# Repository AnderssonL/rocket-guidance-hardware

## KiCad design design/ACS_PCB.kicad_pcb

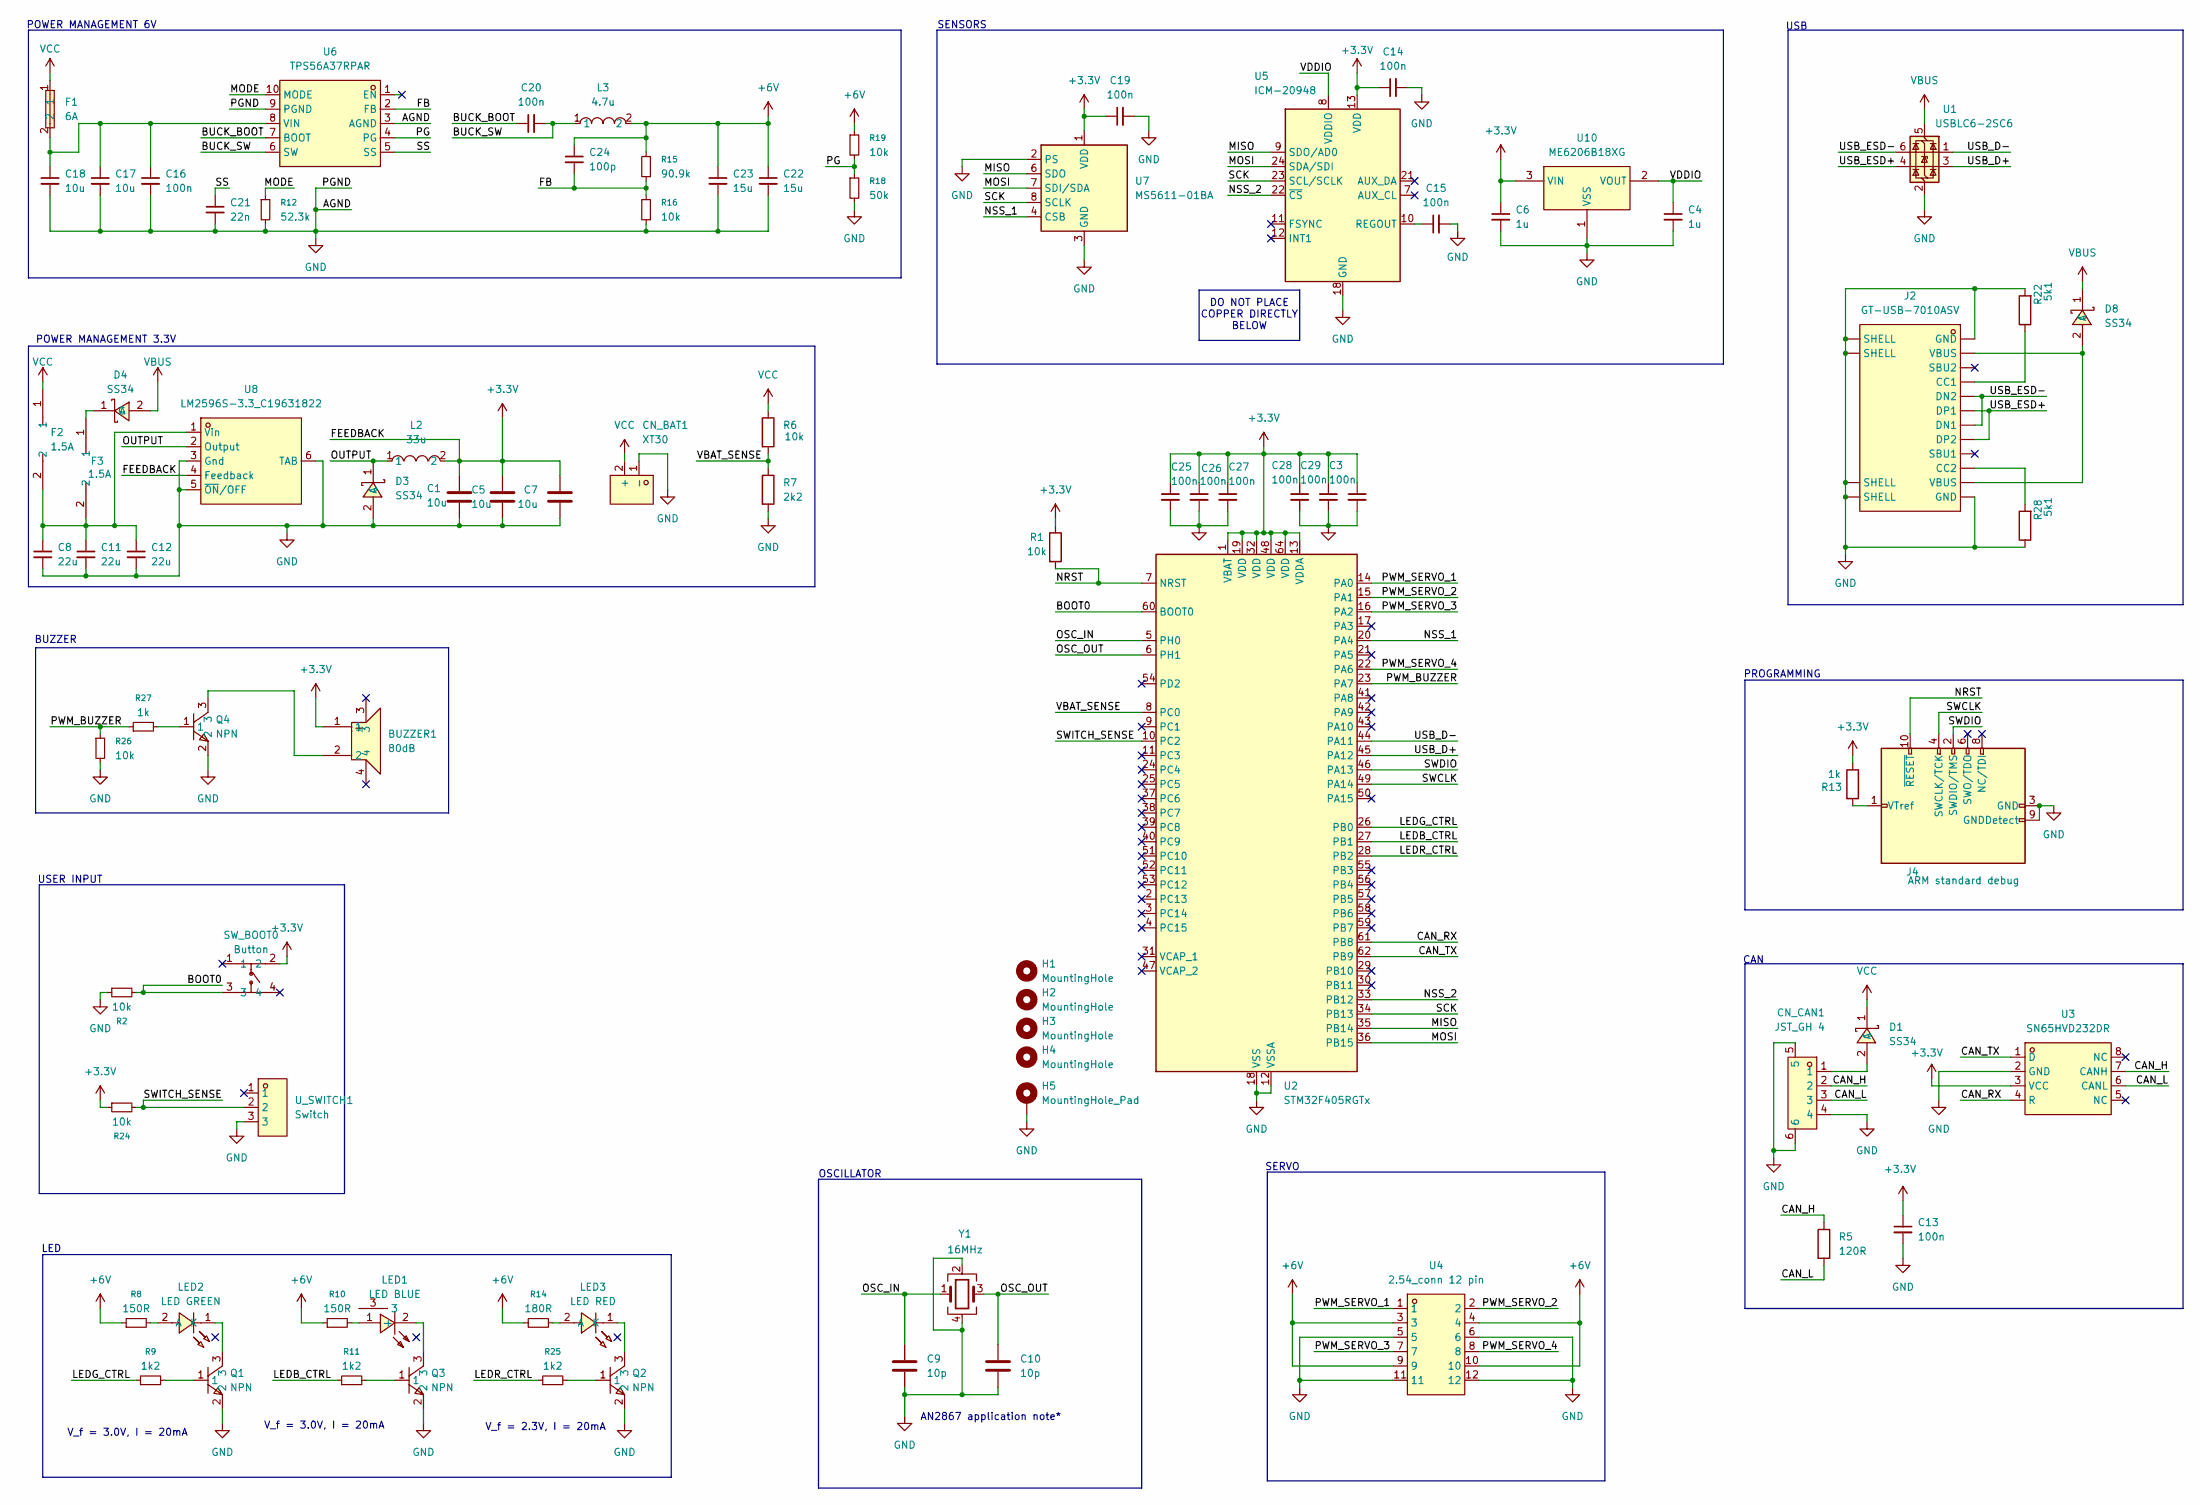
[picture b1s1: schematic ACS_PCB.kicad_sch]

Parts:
BUZZER1: 80dB; BUZ-SMD_4P-L7.5-W7.5-BR; LCSC Part C49246950
C1, C5, C7: 10u; C_0201_0603Metric; LCSC Part C19702
C3, C13, C14, C15, C16, C19, C20, C25, C26, C27, C28, C29: 100n; C_0603_1608Metric; LCSC Part C14663
C4, C6: 1u; C_0603_1608Metric; LCSC Part C15849
C8, C11, C12: 22u; C_0603_1608Metric; LCSC Part C2762594
C9, C10: 10p; C_0603_1608Metric; LCSC Part C1634
C17, C18: 10u; C_0603_1608Metric; LCSC Part C19702
C21: 22n; C_0603_1608Metric; LCSC Part C21122
C22, C23: 15u; C_0603_1608Metric; LCSC Part C445715
C24: 100p; C_0603_1608Metric; LCSC Part C14858
CN_BAT1: XT30; CONN-TH_XT30UPB-M; LCSC Part C428721
CN_CAN1: JST_GH 4; CONN-SMD_4P-P1.25_JXTCONN_DMX-4PWB-43; LCSC Part C42422450
D1, D3, D4, D8: SS34; SMC_L6.9-W5.9-LS7.9-RD; LCSC Part C154551
F1: 6A; F1812; LCSC Part C7542974
F2, F3: 1.5A; F1812; LCSC Part C70117
H1, H2, H3, H4: MountingHole; SMD_BD4.0-D2.5_TH162030CTJ; LCSC Part C3020127
H5: MountingHole_Pad; MountingHole_2.2mm_M2_DIN965_Pad
J2: GT-USB-7010ASV; USB-C-SMD_G-SWITCH_GT-USB-7010ASV; LCSC Part C2988369
J4: ARM standard debug; HDR-SMD_10P-P1.27-V-R2-C5-S5.8; LCSC Part C5155080
L2: 33u; IND-SMD_L6.8-W6.8_SMMS0630; LCSC Part C149577
L3: 4.7u; L0603; LCSC Part C114862
LED1: LED BLUE; LED-SMD_L3.2-W1.0-R-RD; LCSC Part C375481
LED2: LED GREEN; LED1206-RD_GREEN-SIDE; LCSC Part C375564
LED3: LED RED; LED1206-RD_RED_XL-3216SURC-FB; LCSC Part C3646938
Q1, Q2, Q3, Q4: NPN; SOT-23-3_L2.9-W1.3-P1.90-LS2.4-BR; LCSC Part C57668
R1, R2, R6, R16, R19, R24, R26: 10k; R_0603_1608Metric; LCSC Part C98220
R5: 120R; R_0603_1608Metric; LCSC Part C22787
R7: 2k2; R_0603_1608Metric; LCSC Part C114662
R8, R10: 150R; R_0603_1608Metric; LCSC Part C2907103
R9, R11, R25: 1k2; R_0603_1608Metric; LCSC Part C2906976
R12: 52.3k; R_0603_1608Metric; LCSC Part C2998074
R13, R27: 1k; R_0603_1608Metric; LCSC Part C22548
R14: 180R; R_0603_1608Metric; LCSC Part C2907000
R15: 90.9k; R_0603_1608Metric; LCSC Part C2930136
R18: 50k; R_0603_1608Metric; LCSC Part C861451
R22, R28: 5k1; R_0603_1608Metric; LCSC Part C2907044
SW_BOOT0: Button; SW-SMD_4P-L5.2-W5.2-P3.70-LS6.4; LCSC Part C49234134
U1: USBLC6-2SC6; SOT-23-6_L2.9-W1.6-P0.95-LS2.8-BL; LCSC Part C7519
U2: STM32F405RGTx; LQFP-64_10x10mm_P0.5mm; LCSC Part C15742
U3: SN65HVD232DR; SOIC-8_L5.0-W4.0-P1.27-LS6.0-BL; LCSC Part C30530
U4: 2.54_conn 12 pin; HDR-TH_12P-P2.54-V-M-R2-C6-S2.54; LCSC Part C7501277
U5: ICM-20948; InvenSense_QFN-24_3x3mm_P0.4mm
U6: TPS56A37RPAR; VQFN-HR-10_L3.0-W3.0_TI_RPA; LCSC Part C22392669
U7: MS5611-01BA; SENSORS-SMD_MS5611-01BA03; LCSC Part C15639
U8: LM2596S-3.3_C19631822; TO-263-5_L10.2-W9.0-P1.70-TL-LS15.2; LCSC Part C19631822
U10: ME6206B18XG; SOT-23-3_L2.9-W1.3-P1.90-LS2.4-BR; LCSC Part C2683407
U_SWITCH1: Switch; SW-TH_MT-0-102-E001-T000-RS-PJ; LCSC Part C1788499
Y1: 16MHz; CRYSTAL-SMD_4P-L3.2-W2.5-BL; LCSC Part C112972

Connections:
+3.3V: BUZZER1.1, C1.1, C3.1, C5.1, C6.1, C7.1, C13.1, C14.1, C19.1, C25.1, C26.1, C27.1, C28.1, C29.1, L2.2, R1.1, R13.1, R24.1, SW_BOOT0.2, U2.1 (VBAT), U2.13 (VDDA), U2.19 (VDD), U2.32 (VDD), U2.48 (VDD), U2.64 (VDD), U3.3 (VCC), U5.13 (VDD), U7.1 (VDD), U8.4 (Feedback), U10.3 (VIN)
+6V: C22.1, C23.1, C24.1, L3.2, R8.1, R10.1, R14.1, R15.2, R19.1, U4.3, U4.4, U4.9, U4.10
/BOOT0: R2.2, SW_BOOT0.3, U2.60 (BOOT0)
/BUCK_BOOT: C20.1, U6.7 (BOOT)
/BUCK_SW: C20.2, L3.1, U6.6 (SW)
/CAN_H: CN_CAN1.2, R5.1, U3.7 (CANH)
/CAN_L: CN_CAN1.3, R5.2, U3.6 (CANL)
/CAN_RX: U2.61 (PB8), U3.4 (R)
/CAN_TX: U2.62 (PB9), U3.1 (D)
/FB: C24.2, R15.1, R16.2, U6.2 (FB)
/LEDB_CTRL: R11.1, U2.27 (PB1)
/LEDG_CTRL: R9.1, U2.26 (PB0)
/LEDR_CTRL: R25.1, U2.28 (PB2)
/MISO: U2.35 (PB14), U5.9 (SDO/AD0), U7.6 (SDO)
/MODE: R12.1, U6.10 (MODE)
/MOSI: U2.36 (PB15), U5.24 (SDA/SDI), U7.7 (SDI/SDA)
/NRST: J4.10 (~RESET), R1.2, U2.7 (NRST)
/NSS_1: U2.20 (PA4), U7.4 (CSB), U7.5 (CSB)
/NSS_2: U2.33 (PB12), U5.22 (~CS)
/OSC_IN: C9.1, U2.5 (PH0), Y1.1
/OSC_OUT: C10.1, U2.6 (PH1), Y1.3
/OUTPUT: D3.1 (C), L2.1, U8.2 (Output)
/PG: R18.1, R19.2, U6.4 (PG)
/PWM_BUZZER: R26.1, R27.1, U2.23 (PA7)
/PWM_SERVO_1: U2.14 (PA0), U4.1
/PWM_SERVO_2: U2.15 (PA1), U4.2
/PWM_SERVO_3: U2.16 (PA2), U4.7
/PWM_SERVO_4: U2.22 (PA6), U4.8
/SCK: U2.34 (PB13), U5.23 (SCL/SCLK), U7.8 (SCLK)
/SS: C21.1, U6.5 (SS)
/SWCLK: J4.4 (SWCLK/TCK), U2.49 (PA14)
/SWDIO: J4.2 (SWDIO/TMS), U2.46 (PA13)
/SWITCH_SENSE: R24.2, U2.10 (PC2), U_SWITCH1.2
/USB_D+: U1.3 (I/O2), U2.45 (PA12)
/USB_D-: U1.1 (I/O1), U2.44 (PA11)
/USB_ESD+: J2.A6 (DP1), J2.B6 (DP2), U1.4 (I/O2)
/USB_ESD-: J2.A7 (DN1), J2.B7 (DN2), U1.6 (I/O1)
/VBAT_SENSE: R6.2, R7.1, U2.8 (PC0)
/VDDIO: C4.1, U5.8 (VDDIO), U10.2 (VOUT)
GND: C1.2, C3.2, C4.2, C5.2, C6.2, C7.2, C8.2, C9.2, C10.2, C11.2, C12.2, C13.2, C14.2, C15.2, C16.2, C17.2, C18.2, C19.2, C21.2, C22.2, C23.2, C25.2, C26.2, C27.2, C28.2, C29.2, CN_BAT1.1 (-), CN_CAN1.4, CN_CAN1.5, CN_CAN1.6, D3.2 (A), H5.1, J2.1 (SHELL), J2.2 (SHELL), J2.3 (SHELL), J2.4 (SHELL), J2.A1B12 (GND), J2.B1A12 (GND), J4.3 (GND), J4.5 (GND), J4.9 (GNDDetect), Q1.2, Q2.2, Q3.2, Q4.2, R2.1, R7.2, R12.2, R16.1, R18.2, R22.2, R26.2, R28.1, U1.2 (GND), U2.12 (VSSA), U2.18 (VSS), U2.63 (VSS), U3.2 (GND), U4.5, U4.6, U4.11, U4.12, U5.18 (GND), U5.20 (GND), U6.3 (AGND), U6.9 (PGND), U7.2 (PS), U7.3 (GND), U8.3 (Gnd), U8.5 (~ON/OFF), U8.6 (TAB), U10.1 (VSS), U_SWITCH1.3, Y1.2, Y1.4
unnamed: BUZZER1.2, Q4.3
unnamed: CN_CAN1.1, D1.2 (A)
unnamed: D4.1 (C), F3.1
unnamed: D8.2 (A), J2.A4B9 (VBUS), J2.B4A9 (VBUS)
unnamed: J2.A5 (CC1), R22.1
unnamed: J2.B5 (CC2), R28.2
unnamed: J4.1 (VTref), R13.2
unnamed: LED1.1 (+), R10.2
unnamed: LED1.2 (-), Q3.3
unnamed: LED2.2 (A), R8.2
unnamed: LED2.1 (K), Q1.3
unnamed: LED3.2 (A), R14.2
unnamed: LED3.1 (K), Q2.3
unnamed: Q1.1, R9.2
unnamed: Q2.1, R25.2
unnamed: Q3.1, R11.2
unnamed: Q4.1, R27.2
unnamed: C15.1, U5.10 (REGOUT)
unnamed: C16.1, C17.1, C18.1, F1.2, U6.8 (VIN)
unnamed: C8.1, C11.1, C12.1, F2.2, F3.2, U8.1 (Vin)
VBUS: D4.2 (A), D8.1 (C), U1.5 (VBUS)
VCC: CN_BAT1.2 (+), D1.1 (C), F1.1, F2.1, R6.1

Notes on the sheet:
V_f = 3.0V, I = 20mA
BUZZER
SENSORS
USER INPUT
V_f = 2.3V, I = 20mA
LED
POWER MANAGEMENT 6V
POWER MANAGEMENT 3.3V
DO NOT PLACE COPPER DIRECTLY BELOW
OSCILLATOR
SERVO
USB
AN2867 application note*
CAN
PROGRAMMING

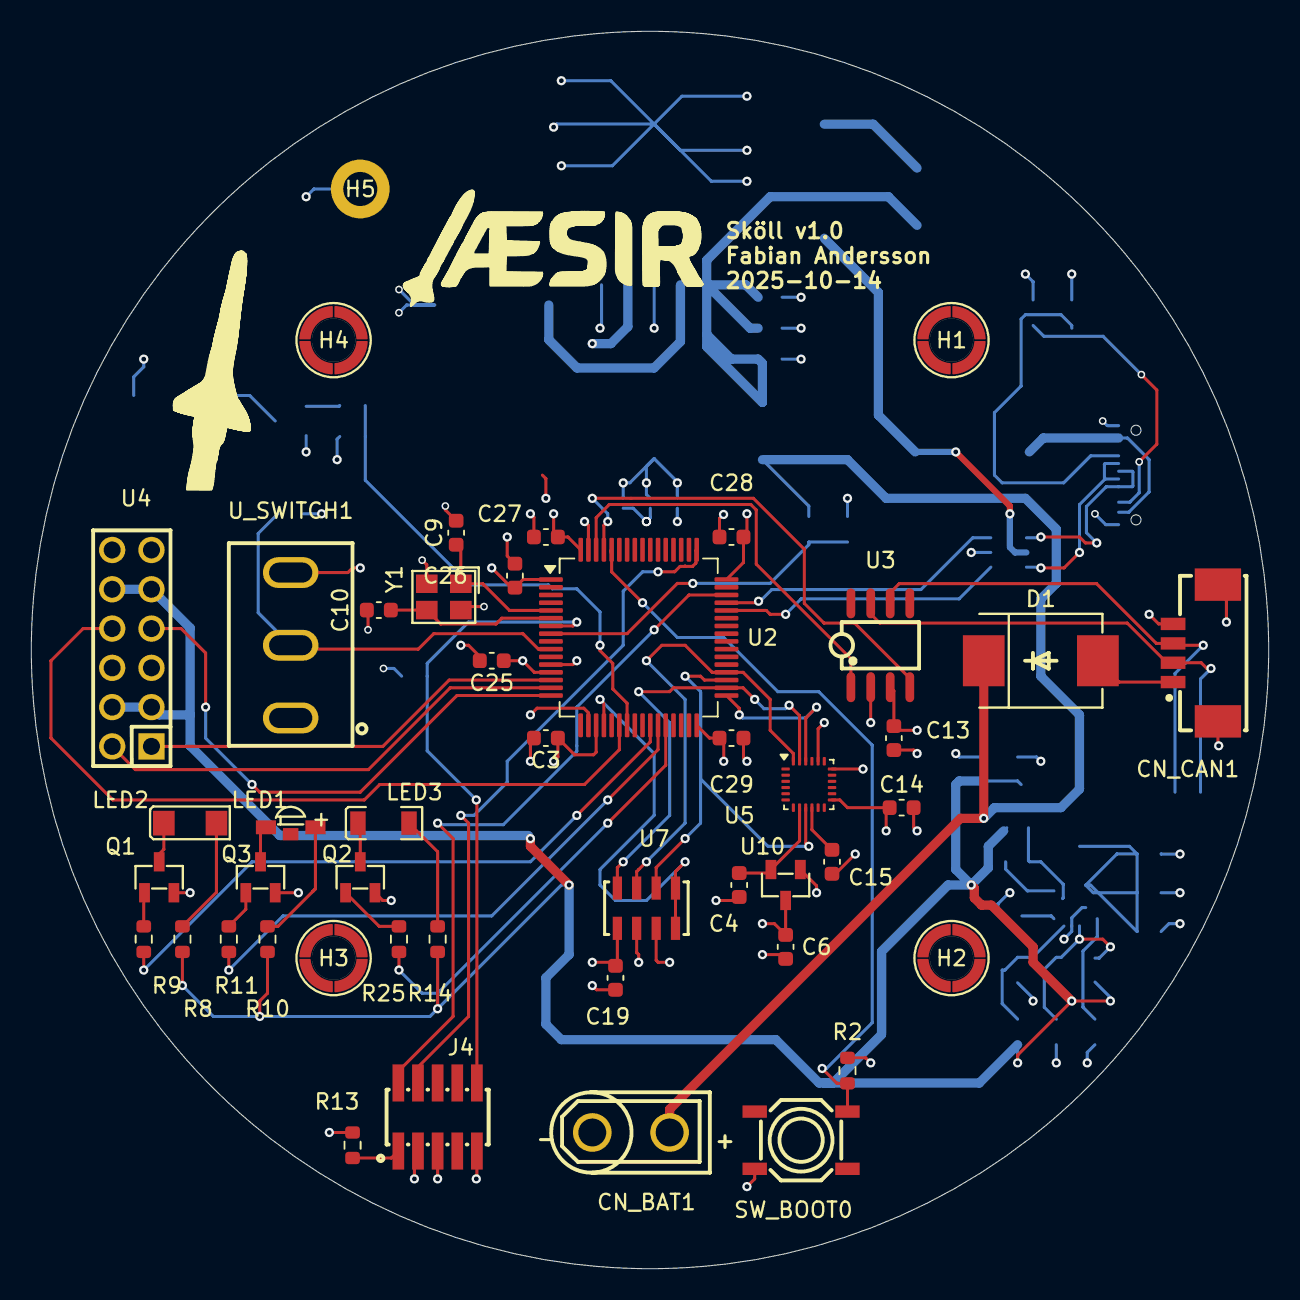
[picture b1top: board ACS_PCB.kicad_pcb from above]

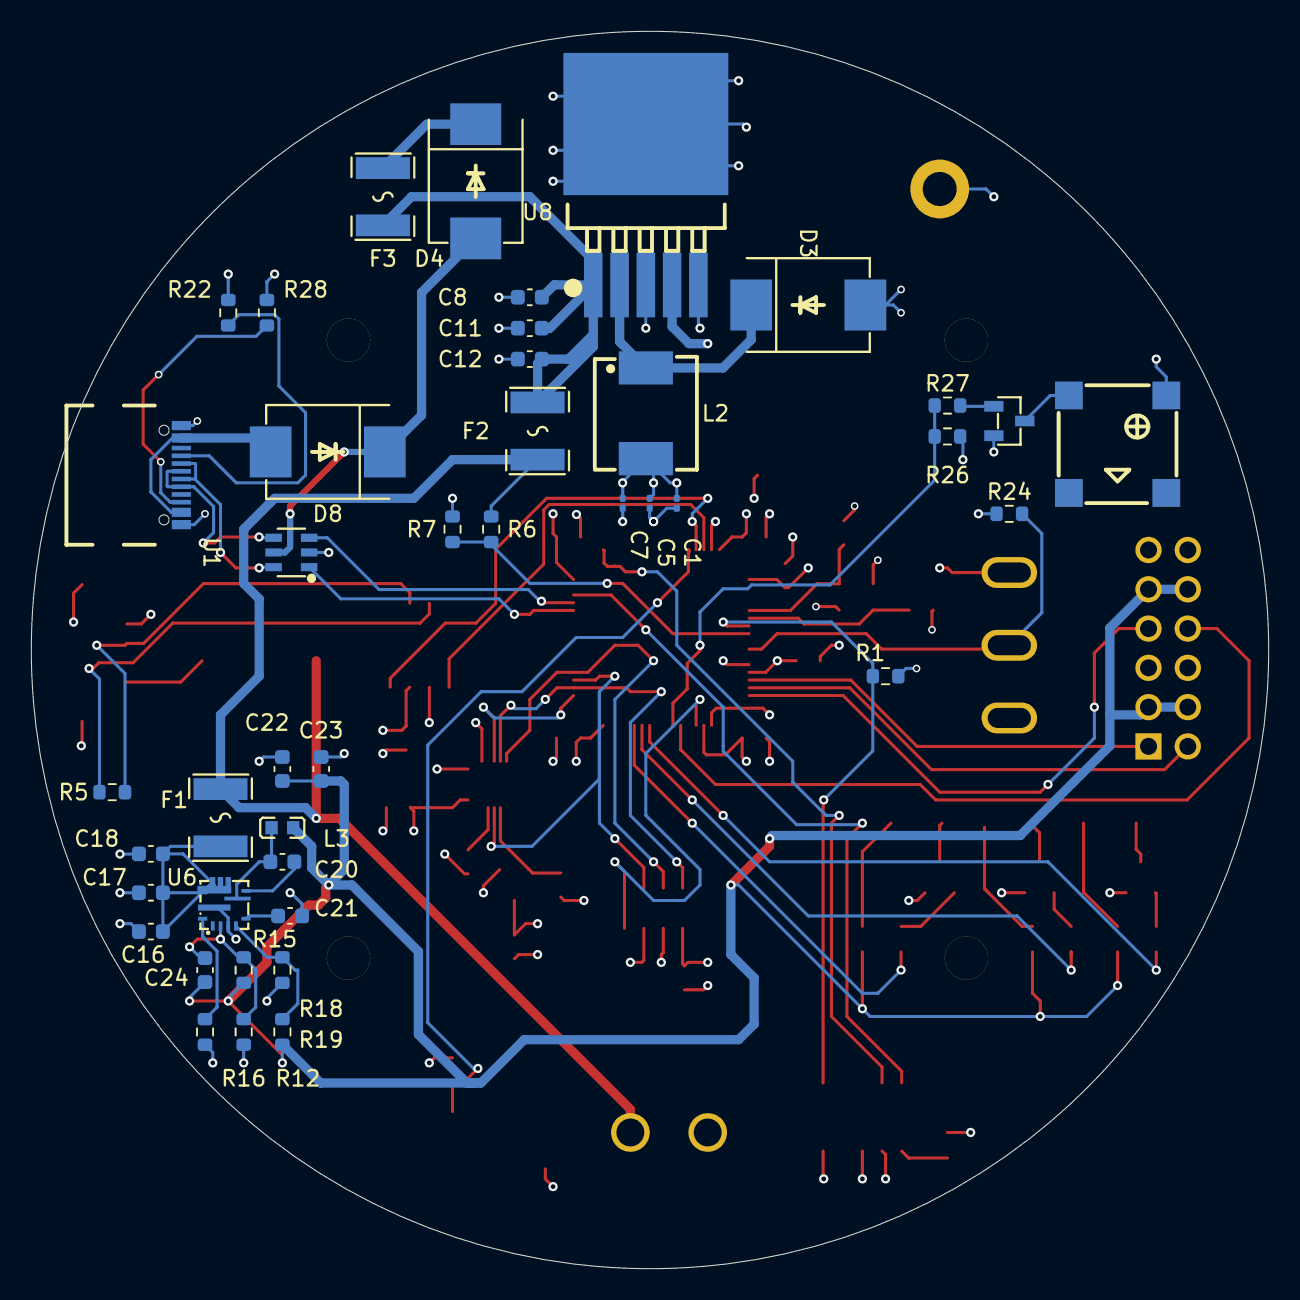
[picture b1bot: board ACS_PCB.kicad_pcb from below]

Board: 4 copper layers, 80.0 x 80.0 mm, 88 parts (42 on the bottom side), 62 nets.

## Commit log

2025-10-09 added design folder
2025-10-09 forgor
2025-10-10 added buzzer, xt30, leds
2025-10-11 added sensors, switch, mounting hole, servo...
2025-10-12 selected LCSC components, small fixes.
2025-10-12 fixed things noted in design review
2025-10-12 placement stuff
2025-10-14 finished layout
2025-10-14 fixed silkscreen texts
2025-10-14 added graphics
2025-10-14 changed to 4 layers
2025-10-14 fixed layout review things (ish)
2025-10-14 fixed some of the suggestions by reviewers
